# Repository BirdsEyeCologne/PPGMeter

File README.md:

# PPGMeter

Developed with Atollic TrueSTUDIO® for STM32, Built on Eclipse Neon.1a. Version: 9.3.0

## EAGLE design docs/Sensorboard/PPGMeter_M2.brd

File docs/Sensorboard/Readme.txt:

Developed with Autodesk Eagle Version 9.5.2
Parts used can be found in lib folder.

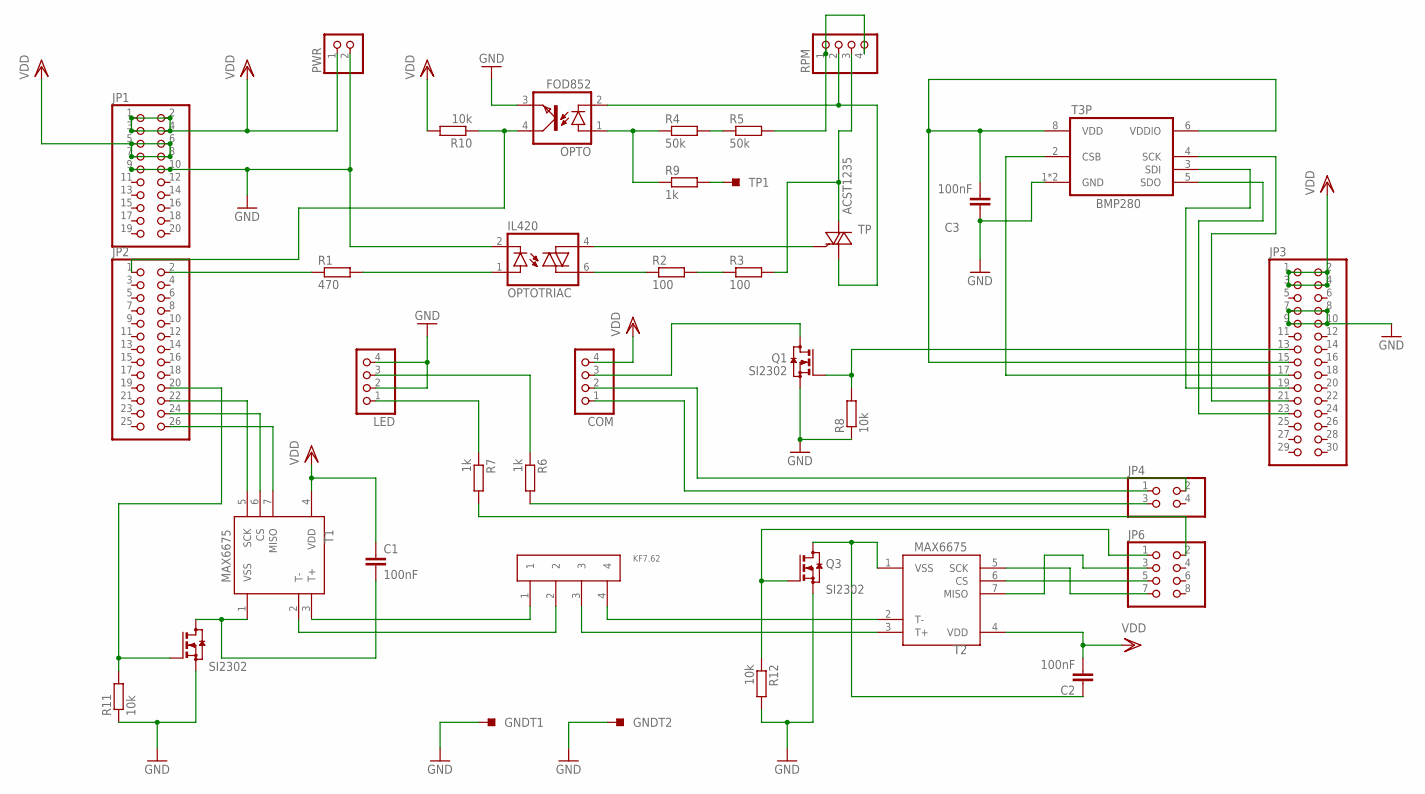
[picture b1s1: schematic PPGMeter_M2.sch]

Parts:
C1, C2, C3: 100nF; C0805K
COM: PINHD-1X4/90; 1X04/90
GNDT1, GNDT2: TPS-SMD-10X25N; SMD-10X25SN
IO1: KF7.62
JP1: PINHD-2X10; 2X10
JP2: PINHD-2X13; 2X13
JP3: PINHD-2X15; 2X15
JP4: PINHD-2X2; 2X02
JP6: PINHD-2X4; 2X04
LED: PINHD-1X4/90; 1X04/90
OPTO: FOD852; SMD4
OPTOTRIAC: IL420; DIL06
PWR: PINHD-1X2/90; 1X02/90
Q1, Q2, Q3: SI2302; SOT23
R1: 470; R0805
R2, R3: 100; R0805
R4, R5: 50k; R0805
R6, R7, R9: 1k; R0805
R8, R10, R11, R12: 10k; R0805
RPM: PINHD-1X4/90; 1X04/90
T1, T2: MAX6675; SO08
T3P: BMP280
TP: ACST1235; TO220AB
TP1: TPS-SMD-10X25N; SMD-10X25SN

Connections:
GND: C3.1, GNDT1.TP, GNDT2.TP, JP1.9, JP1.10, JP3.7, JP3.8, JP3.9, JP3.10, LED.2, LED.4, OPTO.3 (EMIT), OPTOTRIAC.2 (C), PWR.2, Q1.2 (S), Q2.2 (S), Q3.2 (S), R8.1, R11.1, R12.2, T3P.1 (GND), T3P.7 (GND)
LED1: LED.1, R7.1
LED2: LED.3, R6.1
unnamed: JP2.26, T1.7 (MISO)
unnamed: R9.2, TP1.TP
unnamed: JP2.2, R1.1
unnamed: JP6.2, R7.2
unnamed: OPTOTRIAC.1 (A), R1.2
unnamed: OPTOTRIAC.4 (A1), TP.3 (G)
unnamed: R2.2, R3.1
unnamed: R3.2, RPM.3, TP.2 (A2)
unnamed: C1.2, Q2.3 (D), T1.1 (VSS)
unnamed: OPTO.1 (A), R4.1, R9.1
unnamed: R4.2, R5.1
unnamed: JP3.13, Q1.1 (G), R8.2
unnamed: JP2.1, OPTO.4 (COL), R10.1
unnamed: JP2.24, T1.6 (CS)
unnamed: JP2.22, T1.5 (SCK)
unnamed: JP6.7, T2.5 (SCK)
unnamed: JP6.3, T2.7 (MISO)
unnamed: OPTOTRIAC.6 (A2), R2.1
unnamed: JP4.3, R6.2
unnamed: JP2.20, Q2.1 (G), R11.2
unnamed: JP6.5, T2.6 (CS)
unnamed: R5.2, RPM.1, RPM.4
unnamed: C3.2, JP3.15, T3P.6 (VDDIO), T3P.8 (VDD)
unnamed: JP3.21, T3P.4 (SCK)
unnamed: JP3.23, T3P.5 (SDO)
unnamed: COM.3, Q1.3 (D)
unnamed: JP3.17, T3P.2 (CSB)
unnamed: JP3.19, T3P.3 (SDI)
unnamed: IO1.1, T1.3 (T+)
unnamed: OPTO.2 (C), RPM.2, TP.1 (A1)
unnamed: IO1.2, T1.2 (T-)
unnamed: C2.1, Q3.3 (D), T2.1 (VSS)
unnamed: IO1.3, T2.3 (T+)
unnamed: JP6.1, Q3.1 (G), R12.1
unnamed: IO1.4, T2.2 (T-)
RX: COM.1, JP4.1
TX: COM.2, JP4.2
VDD3.3: JP1.5, JP1.6, JP1.7, JP1.8, R10.2
VDD5: COM.4, JP1.1, JP1.2, JP1.3, JP1.4, PWR.1
VDD33: C1.1, C2.2, JP3.1, JP3.2, JP3.3, JP3.4, T1.4 (VDD), T2.4 (VDD)

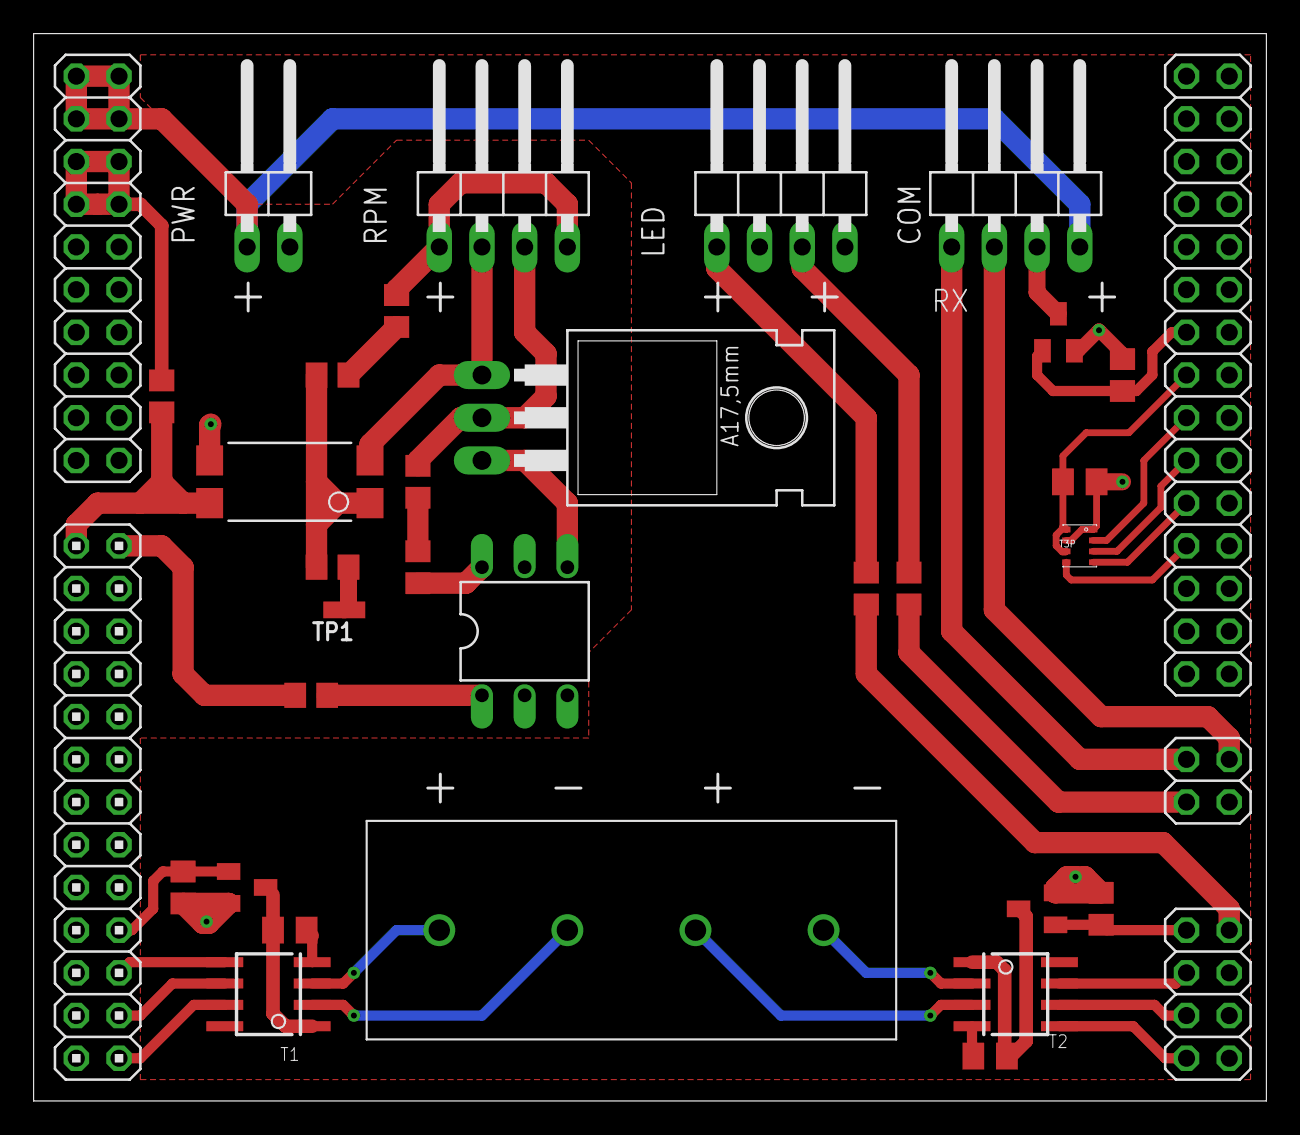
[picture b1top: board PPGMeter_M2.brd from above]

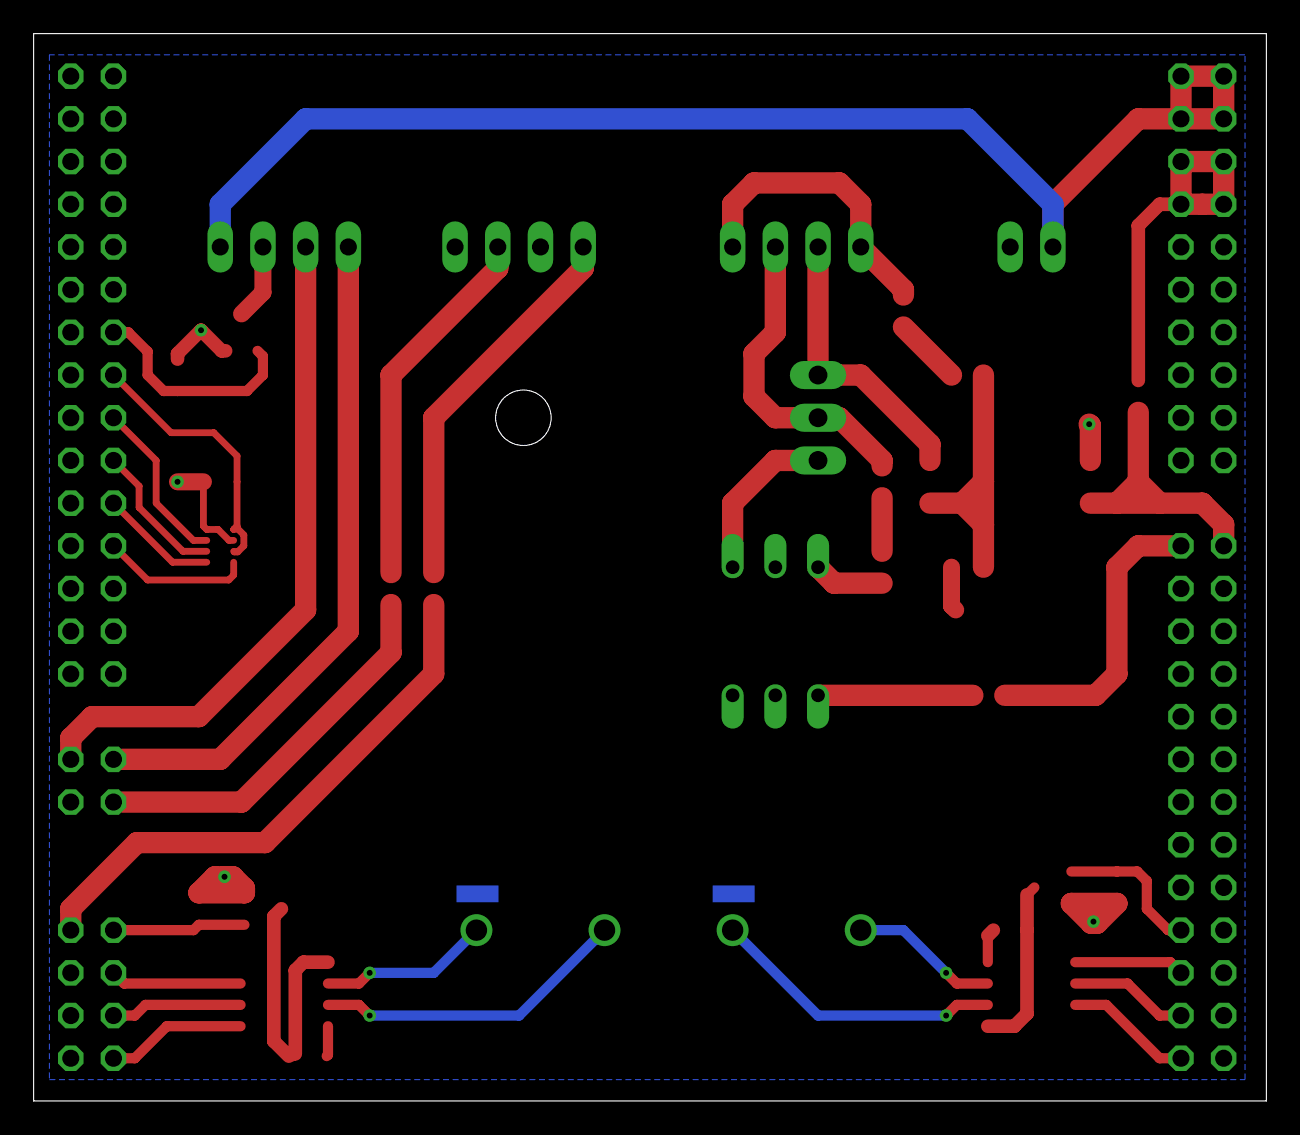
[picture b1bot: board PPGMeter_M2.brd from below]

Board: 2 copper layers, 73.3 x 63.5 mm, 37 parts (2 on the bottom side), 43 nets.

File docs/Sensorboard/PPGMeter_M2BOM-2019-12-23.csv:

Comment,Designator,Footprint
100nF,"C1,C2,C3",C0805K
FOD852,"OPTO",SMD4
SI2302,"Q1,Q2,Q3",SOT23
470,"R1",R0805
100,"R2,R3",R0805
50k,"R4,R5",R0805
1k,"R6,R7,R9",R0805
10k,"R8,R10,R11,R12",R0805
MAX6675,"T1,T2",SO08
BMP280,"T3P",BMP280

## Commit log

2019-11-17 Code Genesis
2019-11-20 Fixed RPM filter issue. Added release hex in bin folder.
2019-12-30 Hardware V1
2019-12-30 Hardware V2
2020-01-01 HW V2, SW V1
2020-01-12 Added android APP and docs.
2020-01-19 Fixed buffer reading in App.
2020-02-16 Increased separation of memory and bluetooth communication (sd dump broken for now)
2020-02-29 New task structure
2020-02-29 Added basic settings (non persistent)

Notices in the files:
parts and their libraries:
TEST: Copyright (C) 2008, Bob Starr
